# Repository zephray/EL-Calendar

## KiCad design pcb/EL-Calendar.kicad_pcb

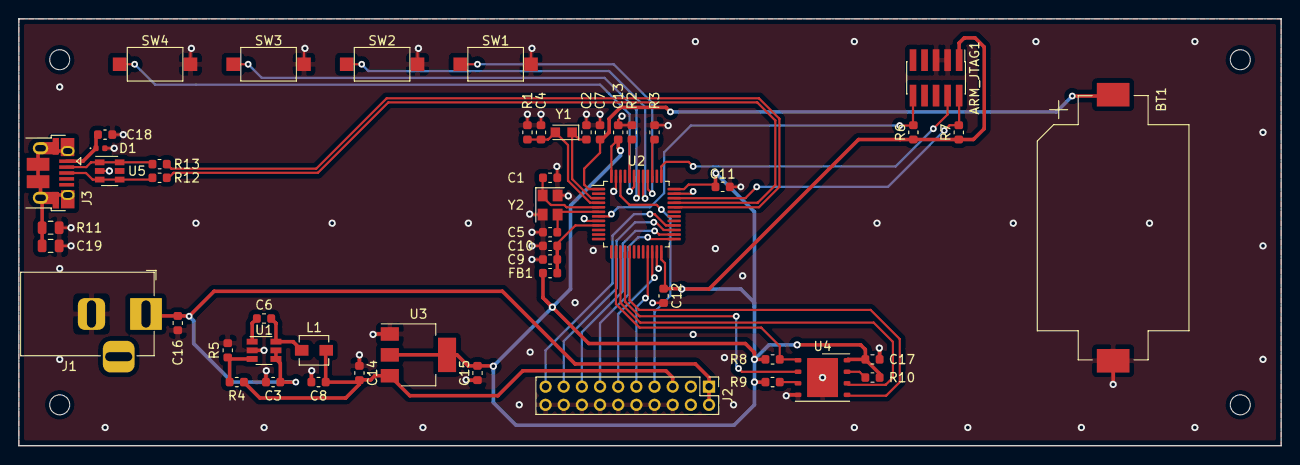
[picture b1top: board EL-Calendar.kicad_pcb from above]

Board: 2 copper layers, 139.0 x 47.0 mm, 51 parts (0 on the bottom side), 41 nets.

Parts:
ARM_JTAG1: Conn_02x05_Odd_Even; PinHeader_2x05_P1.27mm_Vertical_SMD
BT1: CR2032; BatteryHolder_Keystone_1060_1x2032
C1, C2, C4, C5: 18pF; C_0603_1608Metric
C3, C7, C9, C11, C12, C14, C17: 470nF; C_0603_1608Metric
C6: 100nF; C_0603_1608Metric
C8, C15, C16, C18: 10uF; C_0603_1608Metric
C10, C13: 4.7uF; C_0603_1608Metric
C19: 100nF; C_0805_2012Metric
D1: B72590D0050H160; D_0402_1005Metric
FB1: 100R; L_0603_1608Metric
J1: Barrel_Jack_Switch; BarrelJack_Horizontal
J2: Conn_02x10_Odd_Even; PinHeader_2x10_P2.00mm_Vertical
J3: USB_B_Micro; USB_Micro-B_Amphenol_10103594-0001LF_Horizontal
L1: 4.7uH; L_Vishay_IHLP-1212
R1: 2.2M; C_0603_1608Metric
R2, R3, R6, R7: 10K; C_0603_1608Metric
R4: 20K; R_0603_1608Metric
R5: 10K; R_0603_1608Metric
R8, R9, R10: 100K; C_0603_1608Metric
R11: 0; R_0805_2012Metric
R12, R13: 22; C_0603_1608Metric
SW1, SW2, SW3, SW4: SW_Push; SW_SPST_CK_RS282G05A3
U1: SY8120; TSOT-23-6
U2: STM32F103CBTx; LQFP-48_7x7mm_P0.5mm
U3: LM1117-3.3; SOT-223-3_TabPin2
U4: W25Q32JVZP; WSON-8-1EP_6x5mm_P1.27mm_EP3.4x4.3mm
U5: USBLC6-2SC6; SOT-23-6
Y1: Crystal; Crystal_SMD_TXC_9HT11-2Pin_2.0x1.2mm_HandSoldering
Y2: 16MHz; Oscillator_SMD_Abracon_ASE-4Pin_3.2x2.5mm

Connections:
+3V3: ARM_JTAG1.1, C11.1, C12.1, C13.1, C15.2, C17.2, FB1.2, R6.1, R7.1, R8.1, R9.1, R10.1, U2.24, U2.36, U2.48, U3.2, U4.8
+5V: C8.2, C14.2, J2.5, L1.2, R4.2, U3.3
+12V: C3.2, C16.2, J1.1, J2.1, J2.2, U1.4, U1.5
+BATT: BT1.1, C7.1, U2.1
/D0: J2.13, U2.25
/D1: J2.15, U2.26
/D2: J2.17, U2.27
/D3: J2.19, U2.28
/HSYNC: J2.9, U2.21
/KEY1: SW1.1, U2.40
/KEY2: SW2.1, U2.41
/KEY3: SW3.1, U2.42
/KEY4: SW4.1, U2.43
/NRST: ARM_JTAG1.10, R6.2, U2.7
/SPI_CCLK: U2.15, U4.6
/SPI_CS_N: R8.2, U2.14, U4.1
/SPI_MISO: U2.16, U4.2
/SPI_MOSI: U2.17, U4.5
/SWCLK: ARM_JTAG1.4, U2.37
/SWDIO: ARM_JTAG1.2, R7.2, U2.34
/USB_DM: R13.1, U2.32
/USB_DP: R12.1, U2.33
/VCLK: J2.11, U2.22
/VSYNC: J2.7, U2.46
GND: ARM_JTAG1.3, ARM_JTAG1.5, BT1.2, C1.2, C2.1, C3.1, C4.1, C5.2, C7.2, C8.1, C9.2, C10.2, C11.2, C12.2, C13.2, C14.1, C15.1, C16.1, C17.1, C18.2, C19.2, D1.2, J1.2, J2.6, J2.8, J2.10, J2.12, J2.14, J2.16, J2.18, J2.20, R1.2, R2.1, R3.1, R5.1, R11.2, SW1.2, SW2.2, SW3.2, SW4.2, U1.2, U2.8, U2.23, U2.35, U2.47, U3.1, U4.4, U4.9, U5.2, Y2.2, Y2.4
unnamed: C1.1, U2.5, Y2.1
unnamed: C2.2, U2.3, Y1.1
unnamed: C4.2, R1.1, U2.4, Y1.2
unnamed: C5.1, U2.6, Y2.3
unnamed: C6.1, L1.1, U1.6
unnamed: C6.2, U1.1
unnamed: C9.1, C10.1, FB1.1, U2.9
unnamed: C19.1, J3.5, J3.6, R11.1
unnamed: J3.2, R13.2, U5.1, U5.6
unnamed: J3.3, R12.2, U5.3, U5.4
unnamed: R2.2, U2.44
unnamed: R3.2, U2.39
unnamed: R4.1, R5.2, U1.3
unnamed: R9.2, U4.3
unnamed: R10.2, U4.7
VBUS: C18.1, D1.1, J3.1
